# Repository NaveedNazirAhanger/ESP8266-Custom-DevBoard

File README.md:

# ESP8266 Custom Development Board

A custom-designed ESP8266 development board with USB programming capability, voltage regulation, and easy GPIO access. Designed in KiCad for learning PCB design and IoT development.

 *(Coming soon)*

## 🎯 Project Goals

- Design a functional ESP8266 development board from scratch
- Learn PCB design workflow in KiCad
- Create a manufacturable, cost-effective IoT development platform
- Build a reusable tool for future projects

## ✨ Features

- **ESP8266-12E/F WiFi Module** - 802.11 b/g/n connectivity
- **USB Programming** - Direct upload via USB with CH340G USB-to-Serial bridge
- **3.3V Power Regulation** - Onboard AMS1117-3.3 regulator
- **Auto-Reset Circuit** - Automatic bootloader entry for seamless programming
- **GPIO Breakout** - All available pins broken out to headers
- **Status LEDs** - Power and user-programmable LED indicators
- **Flash & Reset Buttons** - Manual control for programming mode
- **Compact Design** - Breadboard-friendly form factor

## 📋 Specifications

| Parameter | Value |
|-----------|-------|
| MCU | ESP8266-12E/F |
| Clock Speed | 80/160 MHz |
| Flash Memory | 4MB |
| Operating Voltage | 3.3V |
| Input Voltage | 5V (USB) |
| Digital I/O | 11 GPIO pins |
| Analog Input | 1x 10-bit ADC |
| WiFi | 802.11 b/g/n |
| USB Interface | Micro-USB / USB-C |

## 🛠️ Hardware Design

### Schematic Overview

The board is organized into functional blocks:

1. **Power Supply** - USB 5V to 3.3V regulation with filtering
2. **USB-to-Serial Bridge** - CH340G for USB communication
3. **ESP8266 Module** - Main MCU with supporting components
4. **Programming Interface** - Auto-reset circuit and manual buttons
5. **GPIO Headers** - Pin breakout for prototyping

### Key Components

- **ESP8266-12E/F** - WiFi SoC module
- **CH340G** - USB-to-UART bridge IC
- **AMS1117-3.3** - 800mA LDO voltage regulator
- **Micro-USB/USB-C Connector** - Power and programming interface
- **BSS138** - N-channel MOSFETs for auto-reset circuit
- Supporting passives (resistors, capacitors, LEDs)

### Bill of Materials (BOM)

See [docs/BOM.md](docs/BOM.md) for complete component list with part numbers and suppliers.

**Estimated Cost:** ~$3-5 per board (components only, excluding PCB)

## 📁 Repository Structure

```
├── hardware/
│   ├── schematic/          # KiCad schematic files
│   ├── pcb/                # KiCad PCB layout files
│   └── gerbers/            # Manufacturing files (Gerber + drill)
├── docs/
│   ├── BOM.md              # Bill of Materials
│   ├── assembly-guide.md   # Assembly instructions
│   └── images/             # Photos, renders, diagrams
├── firmware/
│   └── test-sketches/      # Arduino test programs
└── README.md
```

## 🚀 Getting Started

### Prerequisites

- **KiCad 7.0+** - For viewing/editing design files
- **Arduino IDE** or **PlatformIO** - For programming the board

### Manufacturing

1. Download Gerber files from `hardware/gerbers/`
2. Upload to PCB manufacturer (JLCPCB, PCBWay, OSH Park, etc.)
3. Order components from BOM
4. Assemble board (can be done by hand or use PCBA service)

### Programming

1. Install CH340G drivers if needed
2. Connect board via USB
3. Select "Generic ESP8266 Module" in Arduino IDE
4. Upload code!

See [docs/assembly-guide.md](docs/assembly-guide.md) for detailed instructions.

## 📖 Documentation

- **Schematic PDF:** [hardware/schematic/ESP8266-DevBoard-Schematic.pdf](hardware/schematic/)
- **Assembly Guide:** [docs/assembly-guide.md](docs/assembly-guide.md)
- **BOM:** [docs/BOM.md](docs/BOM.md)
- **Design Notes:** [docs/design-notes.md](docs/design-notes.md)

## 🎓 Learning Resources

This project involves:
- PCB design fundamentals
- Power supply design (linear regulation)
- USB communication circuits
- ESP8266 hardware integration
- Manufacturing-ready design practices

## 🔧 Current Status

- [x] Project planning
- [x] Schematic design
- [x] Footprint assignment
- [x] PCB layout
- [x] PCB routing
- [ ] Design review
- [ ] Prototype order
- [ ] Testing & validation

## 📝 License

This project is open source under the MIT License. See [LICENSE](LICENSE) for details.

## 🤝 Contributing

Suggestions and improvements are welcome! Feel free to open an issue or submit a pull request.

## 👤 Author

**Naveed Nazir**
- GitHub: [@NaveedNazirAhanger](https://github.com/NaveedNazirAhanger)
- Email: naveednazir901@gmail.com
- LinkedIn: [naveed-nazir-0aa270238](https://www.linkedin.com/in/naveed-nazir-0aa270238)

## 🙏 Acknowledgments

- ESP8266 Community for reference designs
- KiCad development team
- Open source hardware movement

---

*This is a learning project for PCB design and embedded systems development.*

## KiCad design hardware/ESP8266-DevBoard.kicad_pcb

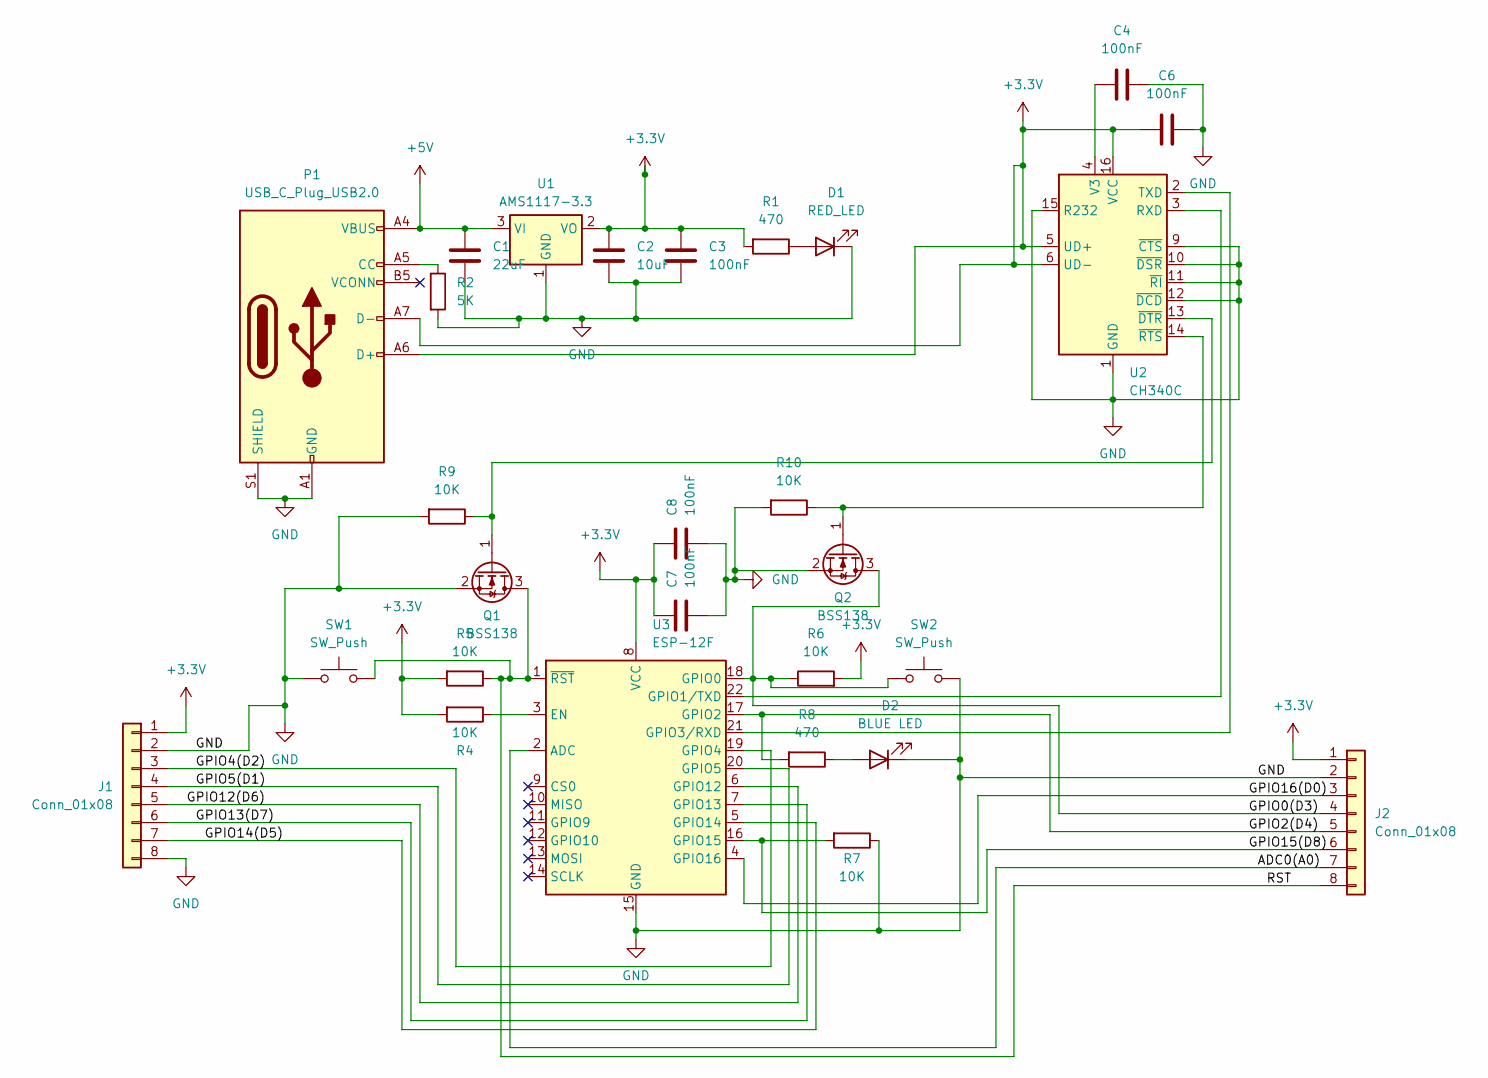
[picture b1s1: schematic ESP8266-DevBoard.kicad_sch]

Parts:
C1: 22uF; C_0805_2012Metric
C2: 10uF; C_0805_2012Metric
C3, C4, C6, C7, C8: 100nF; C_0805_2012Metric
D1: RED_LED; LED_0805_2012Metric
D2: BLUE LED; LED_0805_2012Metric
J1, J2: Conn_01x08; PinHeader_1x08_P2.54mm_Vertical
P1: USB_C_Plug_USB2.0; USB_C_Receptacle_HRO_TYPE-C-31-M-12
Q1, Q2: BSS138; SOT-23
R1, R8: 470; R_0805_2012Metric
R2: 5K; R_0805_2012Metric
R4, R5, R6, R7, R9, R10: 10K; R_0805_2012Metric
SW1, SW2: SW_Push; SW_SPST_B3U-1000P
U1: AMS1117-3.3; SOT-223-3_TabPin2
U2: CH340C; SOIC-16_3.9x9.9mm_P1.27mm
U3: ESP-12F; ESP-12E

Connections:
+3.3V: C2.1, C3.1, C6.2, C7.1, C8.1, J1.1, J2.1, P1.A6 (D+), P1.A7 (D-), R1.2, R4.2, R5.2, R6.2, U1.2 (VO), U2.5 (UD+), U2.6 (UD-), U2.16 (VCC), U3.8 (VCC)
+5V: C1.1, P1.A4 (VBUS), P1.A9 (VBUS), P1.B4 (VBUS), P1.B9 (VBUS), U1.3 (VI)
/ADC0(A0): J2.7, U3.2 (ADC)
/GPIO0(D3): J2.4, Q2.3 (D), R6.1, SW2.1, U3.18 (GPIO0)
/GPIO2(D4): J2.5, R8.2, U3.17 (GPIO2)
/GPIO4(D2): J1.3, U3.19 (GPIO4)
/GPIO5(D1): J1.4, U3.20 (GPIO5)
/GPIO12(D6): J1.5, U3.6 (GPIO12)
/GPIO13(D7): J1.6, U3.7 (GPIO13)
/GPIO14(D5): J1.7, U3.5 (GPIO14)
/GPIO15(D8): J2.6, R7.2, U3.16 (GPIO15)
/GPIO16(D0): J2.3, U3.4 (GPIO16)
/RST: J2.8, Q1.3 (D), R5.1, SW1.2, U3.1 (~RST)
GND: C1.2, C2.2, C3.2, C4.1, C6.1, C7.2, C8.2, D1.1 (K), D2.1 (K), J1.2, J1.8, J2.2, P1.A1 (GND), P1.A12 (GND), P1.B1 (GND), P1.B12 (GND), P1.S1 (SHIELD), Q1.2 (S), Q2.2 (S), R2.2, R7.1, R9.2, R10.2, SW1.1, SW2.2, U1.1 (GND), U2.1 (GND), U2.9 (~CTS), U2.10 (~DSR), U2.11 (~RI), U2.12 (~DCD), U2.15 (R232), U3.15 (GND)
unnamed: D1.2 (A), R1.1
unnamed: D2.2 (A), R8.1
unnamed: P1.A5 (CC), R2.1
unnamed: Q1.1 (G), R9.1, U2.13 (~DTR)
unnamed: Q2.1 (G), R10.1, U2.14 (~RTS)
unnamed: U2.3 (RXD), U3.22 (GPIO1/TXD)
unnamed: U2.2 (TXD), U3.21 (GPIO3/RXD)
unnamed: C4.2, U2.4 (V3)
unnamed: R4.1, U3.3 (EN)

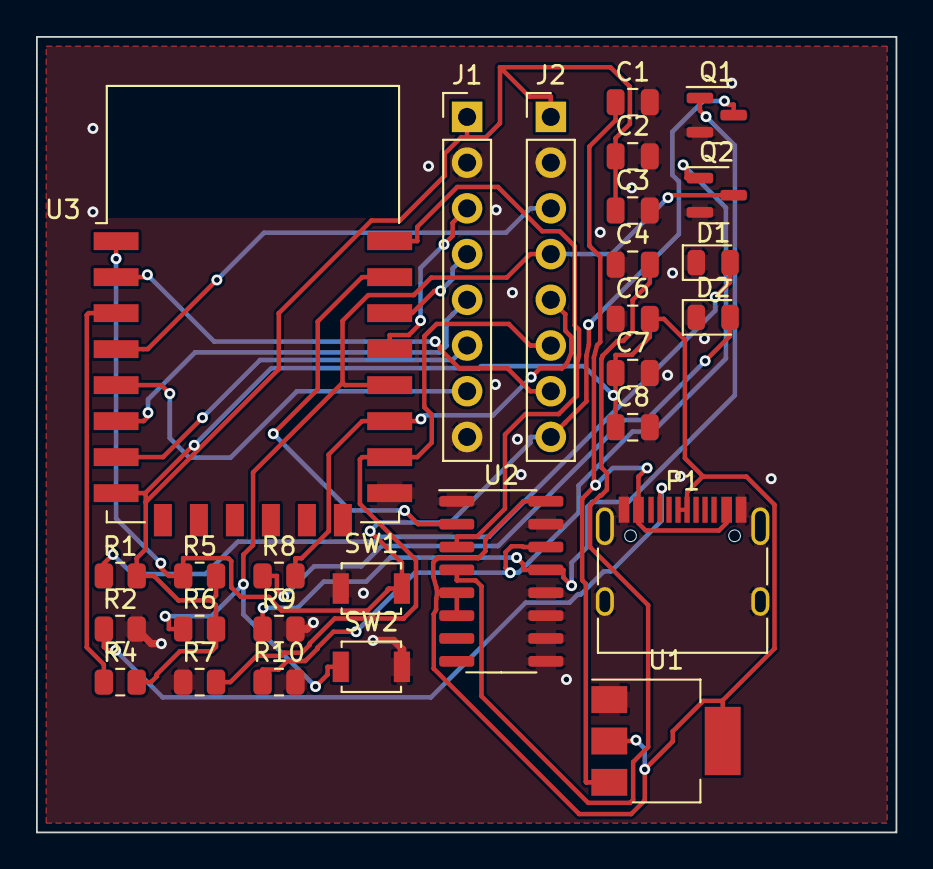
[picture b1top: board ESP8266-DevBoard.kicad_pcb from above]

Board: 2 copper layers, 47.8 x 44.2 mm, 28 parts (0 on the bottom side), 23 nets.

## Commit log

2026-01-14 Complete schematic design with footprint assignments
    - Added power supply circuit (USB-C to 3.3V)
    - CH340C USB-to-serial bridge
    - ESP8266-12F with support circuitry
    - Auto-reset MOSFETs for programming
    - GPIO pin headers
    - All footprints assigned
2026-01-14 Complete schematic design with footprint assignments
    - Power supply circuit (USB-C to 3.3V regulation)
    - CH340C USB-to-serial bridge
    - ESP8266-12F with support circuitry
    - Auto-reset circuit for programming
    - GPIO pin headers
    - All components assigned footprints
2026-01-14 Component placement complete, ready for routing
2026-01-22 Complete PCB routing and layout
    - Routed all power traces (5V, 3.3V, GND)
    - Routed all signal connections (USB, UART, GPIO)
    - Component placement optimized for routing
    - PCB ready for design rule check and manufacturing
    - 2-layer board design
2026-01-22 Update README.md
    PCB routing complete
